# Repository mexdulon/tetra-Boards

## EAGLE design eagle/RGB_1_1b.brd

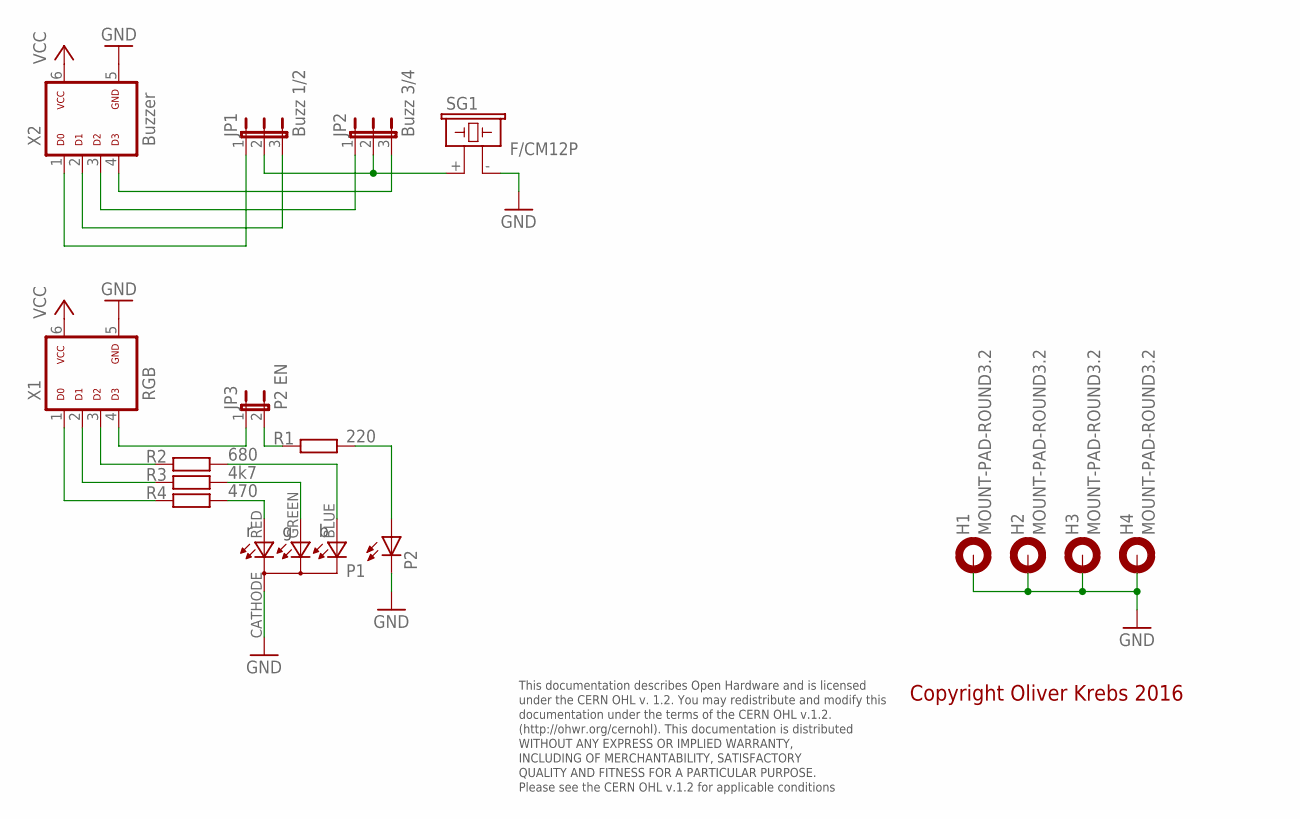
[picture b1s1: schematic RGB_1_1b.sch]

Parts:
H1, H2, H3, H4: MOUNT-PAD-ROUND3.2; 3,2-PAD
JP1: Buzz 1/2; JP2
JP2: Buzz 3/4; JP2
JP3: P2 EN; JP1
P1: RGB-5MM; RGB5MM
P2: LED5MM
R1: 220; 0207/10
R2: 680; 0207/10
R3: 4k7; 0207/10
R4: 470; 0207/10
SG1: F/CM12P
X1: RGB; ML-6
X2: Buzzer; ML-6

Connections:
GND: H1.B3,2, H2.B3,2, H3.B3,2, H4.B3,2, P1.CATHODE, P2.K (C), SG1.- (2), X1.5, X2.5
unnamed: JP1.2, JP2.2, SG1.+ (1)
unnamed: JP3.1, X1.4
unnamed: JP1.1, X2.1
unnamed: JP1.3, X2.2
unnamed: JP2.1, X2.3
unnamed: JP2.3, X2.4
unnamed: R2.1, X1.3
unnamed: R4.1, X1.1
unnamed: R3.1, X1.2
unnamed: P1.RED (A-RED), R4.2
unnamed: P1.GREEN (A-GREEN), R3.2
unnamed: P1.BLUE (A-BLUE), R2.2
unnamed: P2.A, R1.2
unnamed: JP3.2, R1.1
VCC: X1.6, X2.6

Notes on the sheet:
This documentation describes Open Hardware and is licensed under the CERN OHL v. 1.2. You may redistribute and modify this documentation under the terms of the CERN OHL v.1.2. (http://ohwr.org/cernohl). This documentation is distributed WITHOUT ANY EXPRESS OR IMPLIED WARRANTY, INCLUDING OF MERCHANT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
Copyright Oliver Krebs 2016

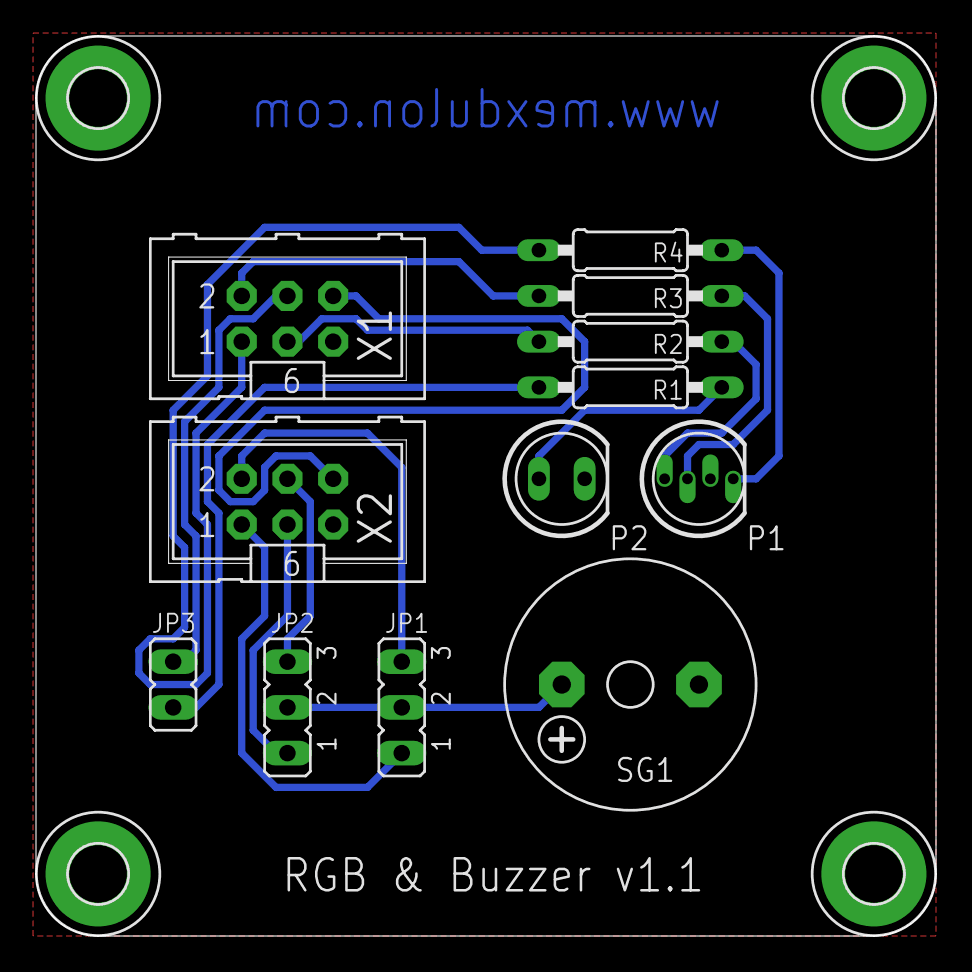
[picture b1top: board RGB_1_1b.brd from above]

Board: 2 copper layers, 50.0 x 50.0 mm, 16 parts (0 on the bottom side), 16 nets.

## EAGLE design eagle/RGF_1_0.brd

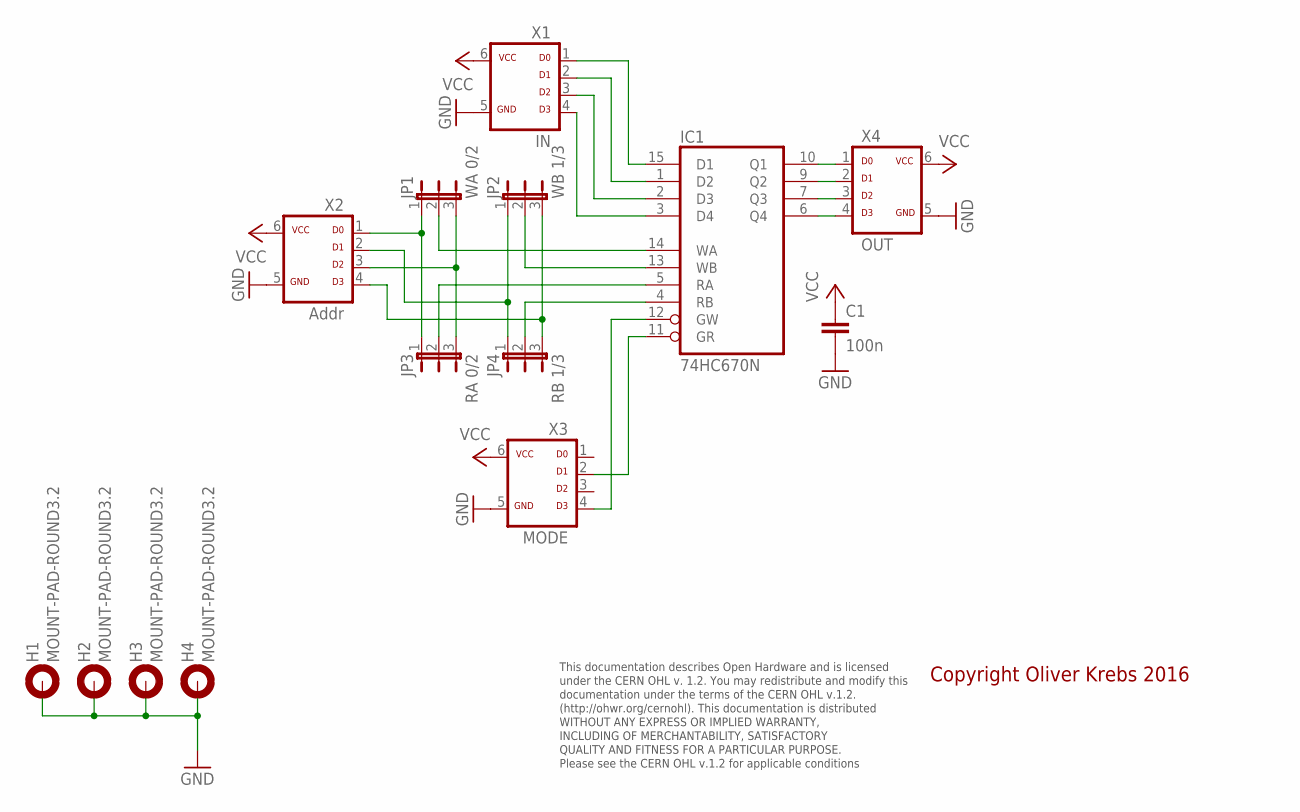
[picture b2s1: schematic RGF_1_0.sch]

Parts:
C1: 100n; C050-025X075
H1, H2, H3, H4: MOUNT-PAD-ROUND3.2; 3,2-PAD
IC1: 74HC670N; DIL16
JP1: WA 0/2; JP2
JP2: WB 1/3; JP2
JP3: RA 0/2; JP2
JP4: RB 1/3; JP2
X1: IN; ML-6
X2: Addr; ML-6
X3: MODE; ML-6
X4: OUT; ML-6

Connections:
GND: C1.2, H1.B3,2, H2.B3,2, H3.B3,2, H4.B3,2, IC1.8 (GND), X1.5, X2.5, X3.5, X4.5
unnamed: IC1.15 (D1), X1.1
unnamed: IC1.1 (D2), X1.2
unnamed: IC1.2 (D3), X1.3
unnamed: IC1.3 (D4), X1.4
unnamed: IC1.9 (Q2), X4.2
unnamed: IC1.10 (Q1), X4.1
unnamed: IC1.7 (Q3), X4.3
unnamed: IC1.6 (Q4), X4.4
unnamed: JP1.1, JP3.1, X2.1
unnamed: JP1.3, JP3.3, X2.3
unnamed: IC1.14 (WA), JP1.2
unnamed: IC1.13 (WB), JP2.2
unnamed: JP2.3, JP4.3, X2.4
unnamed: JP2.1, JP4.1, X2.2
unnamed: IC1.4 (RB), JP4.2
unnamed: IC1.5 (RA), JP3.2
unnamed: IC1.12 (GW), X3.4
unnamed: IC1.11 (GR), X3.2
VCC: C1.1, IC1.16 (VCC), X1.6, X2.6, X3.6, X4.6

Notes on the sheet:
This documentation describes Open Hardware and is licensed under the CERN OHL v. 1.2. You may redistribute and modify this documentation under the terms of the CERN OHL v.1.2. (http://ohwr.org/cernohl). This documentation is distributed WITHOUT ANY EXPRESS OR IMPLIED WARRANTY, INCLUDING OF MERCHANT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
Copyright Oliver Krebs 2016

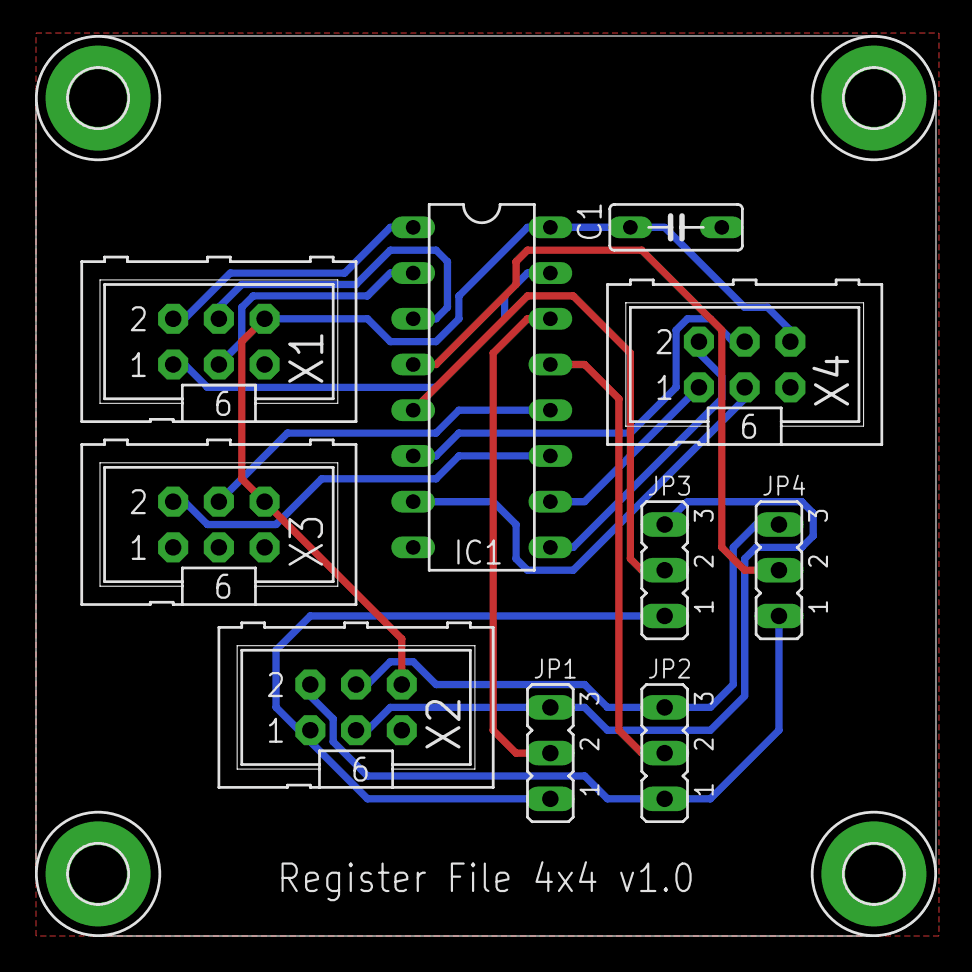
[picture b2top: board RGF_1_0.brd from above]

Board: 2 copper layers, 50.0 x 50.0 mm, 14 parts (0 on the bottom side), 20 nets.

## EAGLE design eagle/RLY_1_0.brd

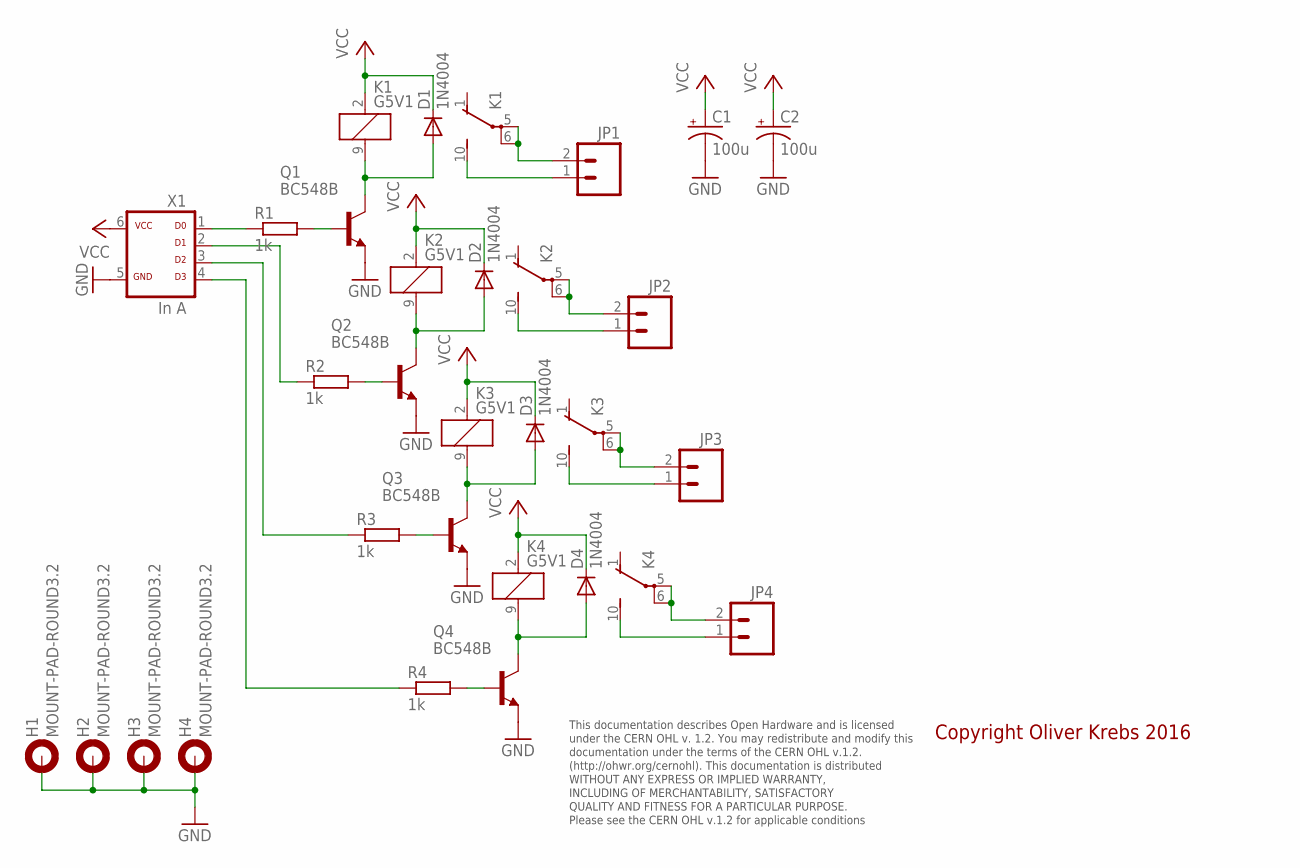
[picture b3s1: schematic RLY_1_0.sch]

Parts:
C1, C2: 100u; CPOL-RADIAL-100UF-25V
D1, D2, D3, D4: 1N4004; DO41-10
H1, H2, H3, H4: MOUNT-PAD-ROUND3.2; 3,2-PAD
JP1, JP2, JP3, JP4: M021.3MM-5.08; 1X02_BIG_5.08
K1, K2, K3, K4: G5V1
Q1, Q2, Q3, Q4: BC548B; TO92-EBC
R1, R2, R3, R4: 1k; 0207/10
X1: In A; ML-6

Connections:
GND: C1.2 (-), C2.2 (-), H1.B3,2, H2.B3,2, H3.B3,2, H4.B3,2, Q1.E, Q2.E, Q3.E, Q4.E, X1.5
unnamed: Q1.B, R1.2
unnamed: D1.A, K1.9 (2), Q1.C
unnamed: JP1.1, K1.10 (S)
unnamed: JP1.2, K1.5, K1.6
unnamed: Q2.B, R2.2
unnamed: D2.A, K2.9 (2), Q2.C
unnamed: JP2.1, K2.10 (S)
unnamed: JP2.2, K2.5, K2.6
unnamed: Q3.B, R3.2
unnamed: D3.A, K3.9 (2), Q3.C
unnamed: JP3.1, K3.10 (S)
unnamed: JP3.2, K3.5, K3.6
unnamed: Q4.B, R4.2
unnamed: D4.A, K4.9 (2), Q4.C
unnamed: JP4.1, K4.10 (S)
unnamed: JP4.2, K4.5, K4.6
unnamed: R1.1, X1.1
unnamed: R2.1, X1.2
unnamed: R3.1, X1.3
unnamed: R4.1, X1.4
VCC: C1.1 (+), C2.1 (+), D1.C, D2.C, D3.C, D4.C, K1.2 (1), K2.2 (1), K3.2 (1), K4.2 (1), X1.6

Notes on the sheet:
This documentation describes Open Hardware and is licensed under the CERN OHL v. 1.2. You may redistribute and modify this documentation under the terms of the CERN OHL v.1.2. (http://ohwr.org/cernohl). This documentation is distributed WITHOUT ANY EXPRESS OR IMPLIED WARRANTY, INCLUDING OF MERCHANT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
Copyright Oliver Krebs 2016

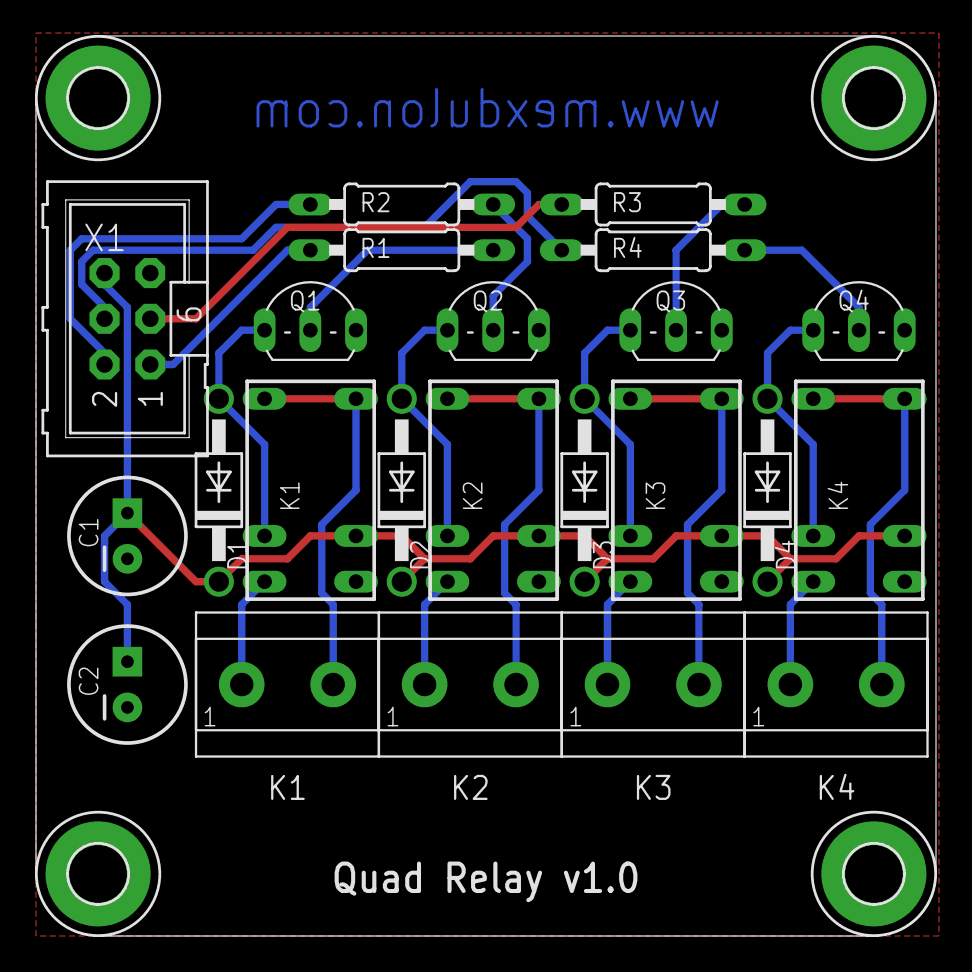
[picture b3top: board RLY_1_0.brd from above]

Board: 2 copper layers, 50.0 x 50.0 mm, 27 parts (0 on the bottom side), 22 nets.

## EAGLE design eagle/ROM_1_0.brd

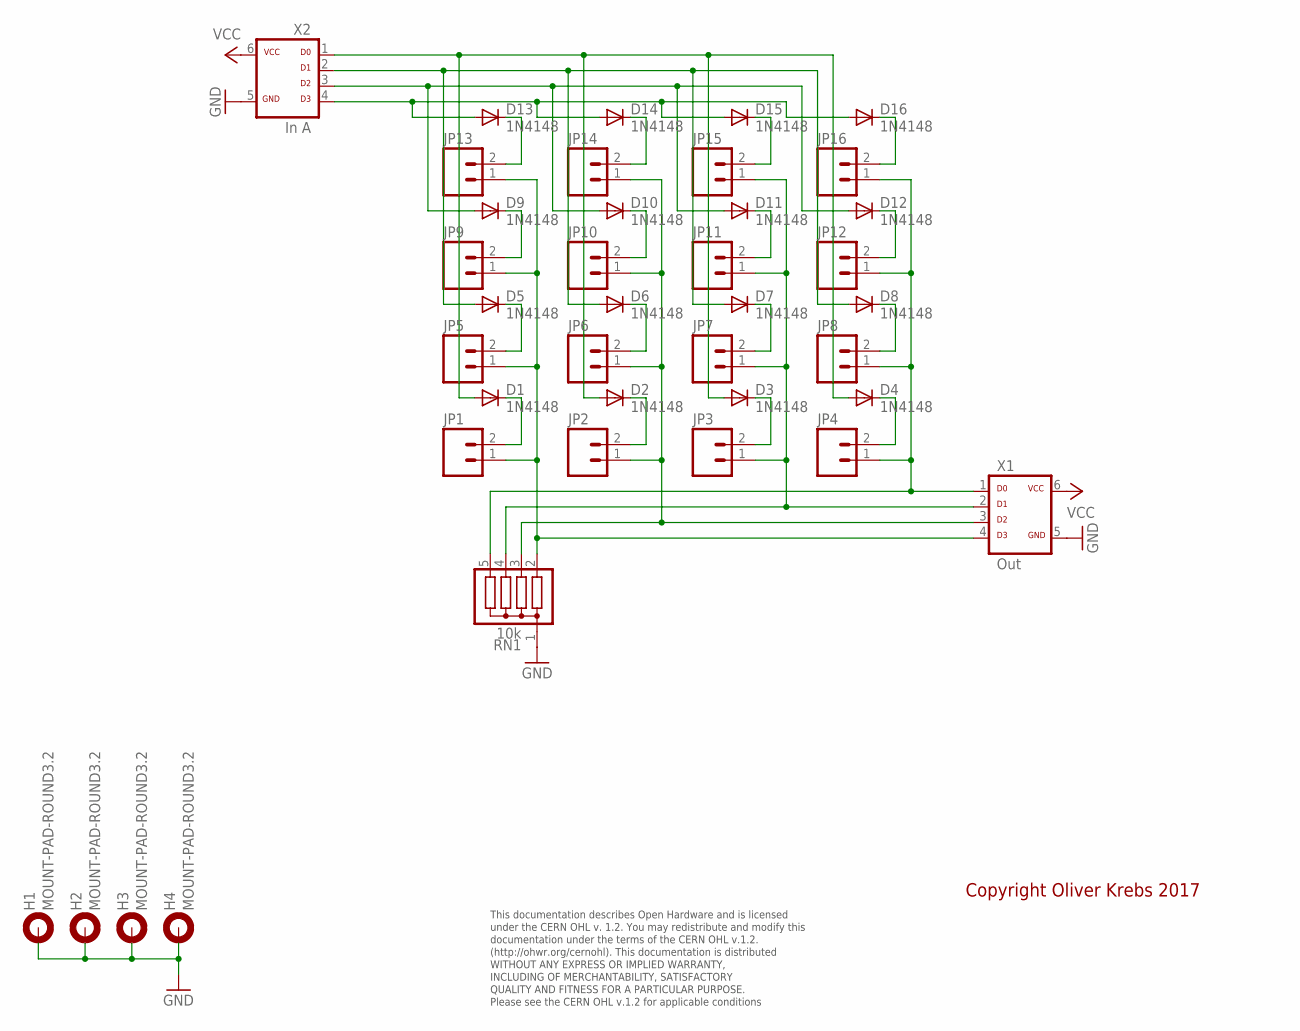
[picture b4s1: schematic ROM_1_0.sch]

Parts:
D1, D2, D3, D4, D5, D6, D7, D8, D9, D10, D11, D12, D13, D14, D15, D16: 1N4148; DO35-7
H1, H2, H3, H4: MOUNT-PAD-ROUND3.2; 3,2-PAD
JP1, JP2, JP3, JP4, JP5, JP6, JP7, JP8, JP9, JP10, JP11, JP12, JP13, JP14, JP15, JP16: M02PTH; 1X02
RN1: 10k; SIL5
X1: Out; ML-6
X2: In A; ML-6

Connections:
GND: H1.B3,2, H2.B3,2, H3.B3,2, H4.B3,2, RN1.1, X1.5, X2.5
unnamed: JP4.1, JP8.1, JP12.1, JP16.1, RN1.5, X1.1
unnamed: JP3.1, JP7.1, JP11.1, JP15.1, RN1.4, X1.2
unnamed: JP2.1, JP6.1, JP10.1, JP14.1, RN1.3, X1.3
unnamed: JP1.1, JP5.1, JP9.1, JP13.1, RN1.2, X1.4
unnamed: D1.A, D2.A, D3.A, D4.A, X2.1
unnamed: D1.C, JP1.2
unnamed: D2.C, JP2.2
unnamed: D3.C, JP3.2
unnamed: D4.C, JP4.2
unnamed: D5.A, D6.A, D7.A, D8.A, X2.2
unnamed: D6.C, JP6.2
unnamed: D7.C, JP7.2
unnamed: D5.C, JP5.2
unnamed: D8.C, JP8.2
unnamed: D9.C, JP9.2
unnamed: D10.C, JP10.2
unnamed: D11.C, JP11.2
unnamed: D12.C, JP12.2
unnamed: D9.A, D10.A, D11.A, D12.A, X2.3
unnamed: D13.A, D14.A, D15.A, D16.A, X2.4
unnamed: D13.C, JP13.2
unnamed: D14.C, JP14.2
unnamed: D15.C, JP15.2
unnamed: D16.C, JP16.2
VCC: X1.6, X2.6

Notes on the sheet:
This documentation describes Open Hardware and is licensed under the CERN OHL v. 1.2. You may redistribute and modify this documentation under the terms of the CERN OHL v.1.2. (http://ohwr.org/cernohl). This documentation is distributed WITHOUT ANY EXPRESS OR IMPLIED WARRANTY, INCLUDING OF MERCHANT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
Copyright Oliver Krebs 2017

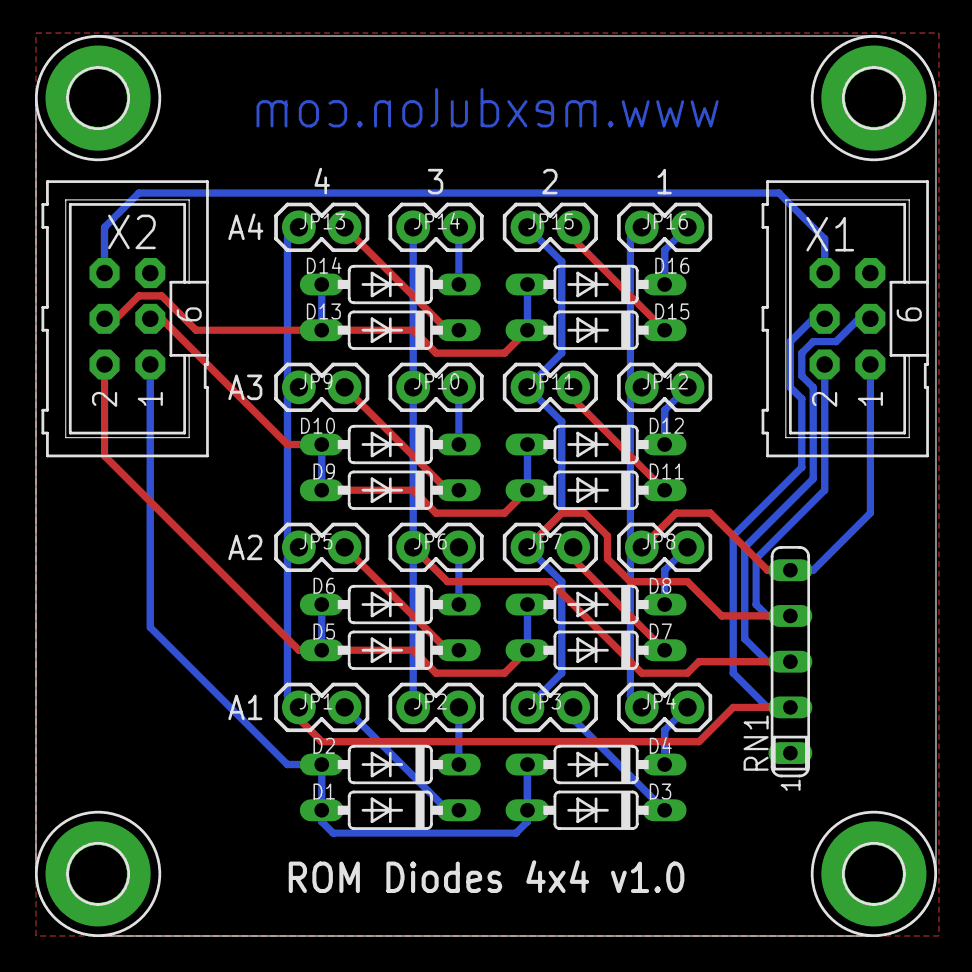
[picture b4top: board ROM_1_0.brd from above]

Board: 2 copper layers, 50.0 x 50.0 mm, 39 parts (0 on the bottom side), 26 nets.

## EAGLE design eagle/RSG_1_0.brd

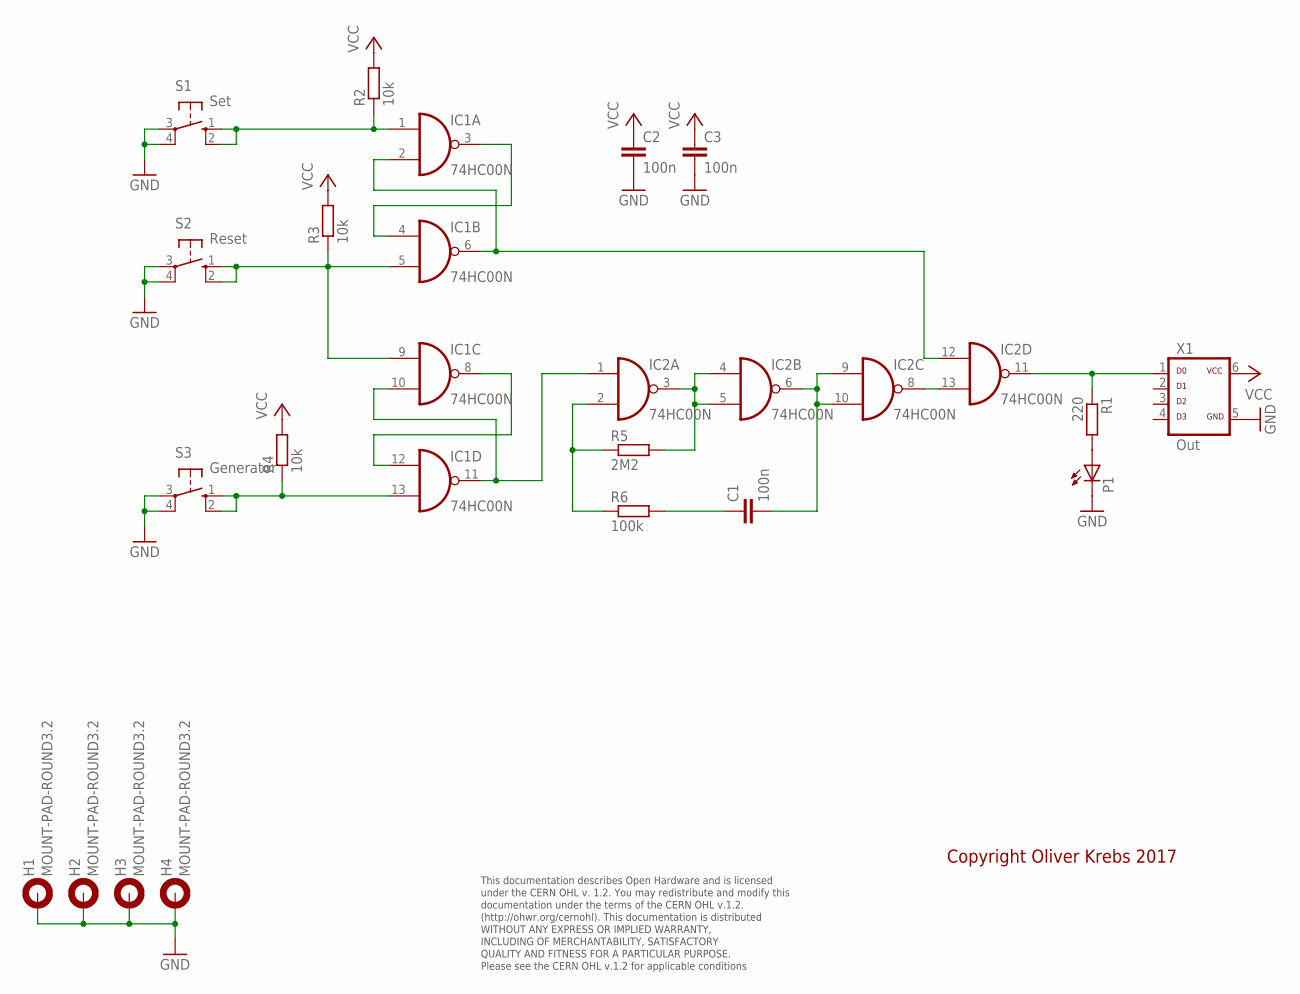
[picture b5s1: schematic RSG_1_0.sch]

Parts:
C1, C2, C3: 100n; C050-025X075
H1, H2, H3, H4: MOUNT-PAD-ROUND3.2; 3,2-PAD
IC1, IC2: 74HC00N; DIL14
P1: LED3MM
R1: 220; 0207/10
R2, R3, R4: 10k; 0207/10
R5: 2M2; 0207/10
R6: 100k; 0207/10
S1: Set; B3F-10XX
S2: Reset; B3F-10XX
S3: Generator; B3F-10XX
X1: Out; ML-6

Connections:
GND: C2.2, C3.2, H1.B3,2, H2.B3,2, H3.B3,2, H4.B3,2, IC1.7 (GND), IC2.7 (GND), P1.K (C), S1.3, S1.4 (P1), S2.3, S2.4 (P1), S3.3, S3.4 (P1), X1.5
unnamed: IC1.1 (I0), R2.1, S1.1 (S), S1.2 (S1)
unnamed: IC1.2 (I1), IC1.6 (O), IC2.12 (I0)
unnamed: IC1.3 (O), IC1.4 (I0)
unnamed: IC1.5 (I1), IC1.9 (I0), R3.1, S2.1 (S), S2.2 (S1)
unnamed: IC1.13 (I1), R4.1, S3.1 (S), S3.2 (S1)
unnamed: IC1.10 (I1), IC1.11 (O), IC2.1 (I0)
unnamed: IC1.8 (O), IC1.12 (I0)
unnamed: IC2.3 (O), IC2.4 (I0), IC2.5 (I1), R5.2
unnamed: P1.A, R1.2
unnamed: C1.2, IC2.6 (O), IC2.9 (I0), IC2.10 (I1)
unnamed: IC2.8 (O), IC2.13 (I1)
unnamed: IC2.11 (O), R1.1, X1.1
unnamed: IC2.2 (I1), R5.1, R6.1
unnamed: C1.1, R6.2
VCC: C2.1, C3.1, IC1.14 (VCC), IC2.14 (VCC), R2.2, R3.2, R4.2, X1.6

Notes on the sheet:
This documentation describes Open Hardware and is licensed under the CERN OHL v. 1.2. You may redistribute and modify this documentation under the terms of the CERN OHL v.1.2. (http://ohwr.org/cernohl). This documentation is distributed WITHOUT ANY EXPRESS OR IMPLIED WARRANTY, INCLUDING OF MERCHANT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
Copyright Oliver Krebs 2017

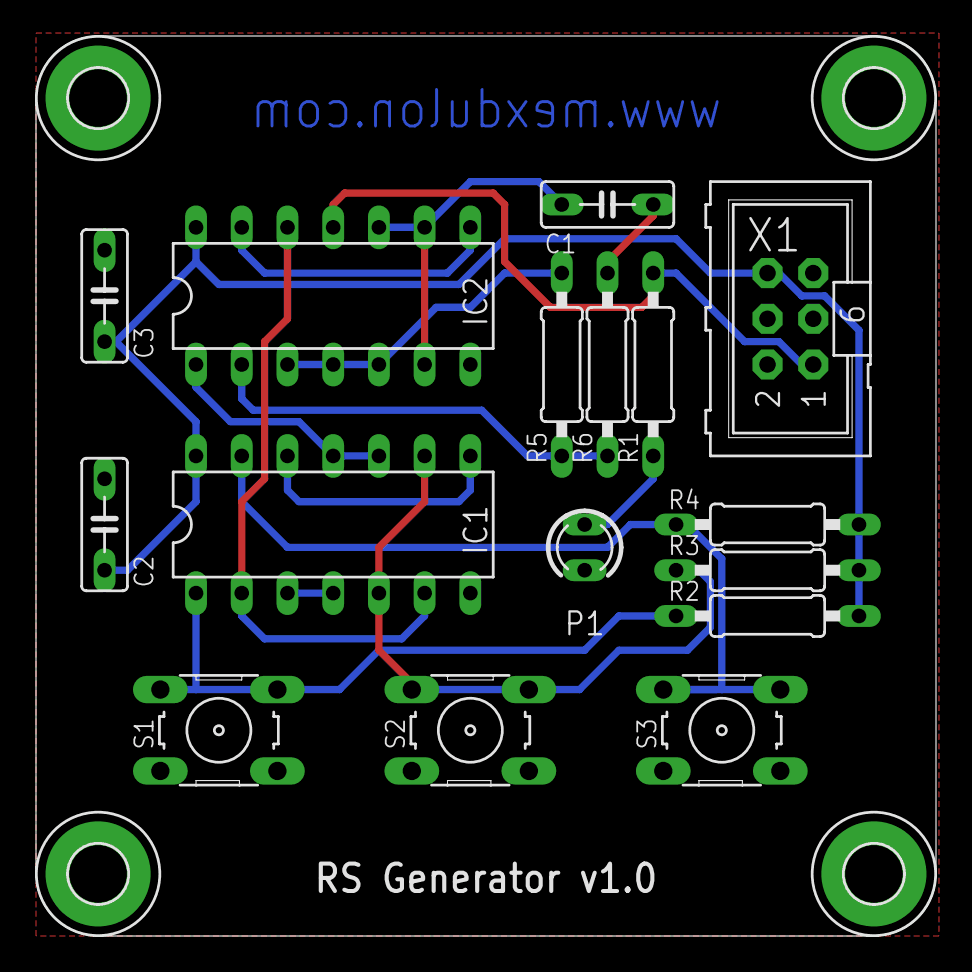
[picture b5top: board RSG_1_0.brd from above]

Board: 2 copper layers, 50.0 x 50.0 mm, 20 parts (0 on the bottom side), 16 nets.

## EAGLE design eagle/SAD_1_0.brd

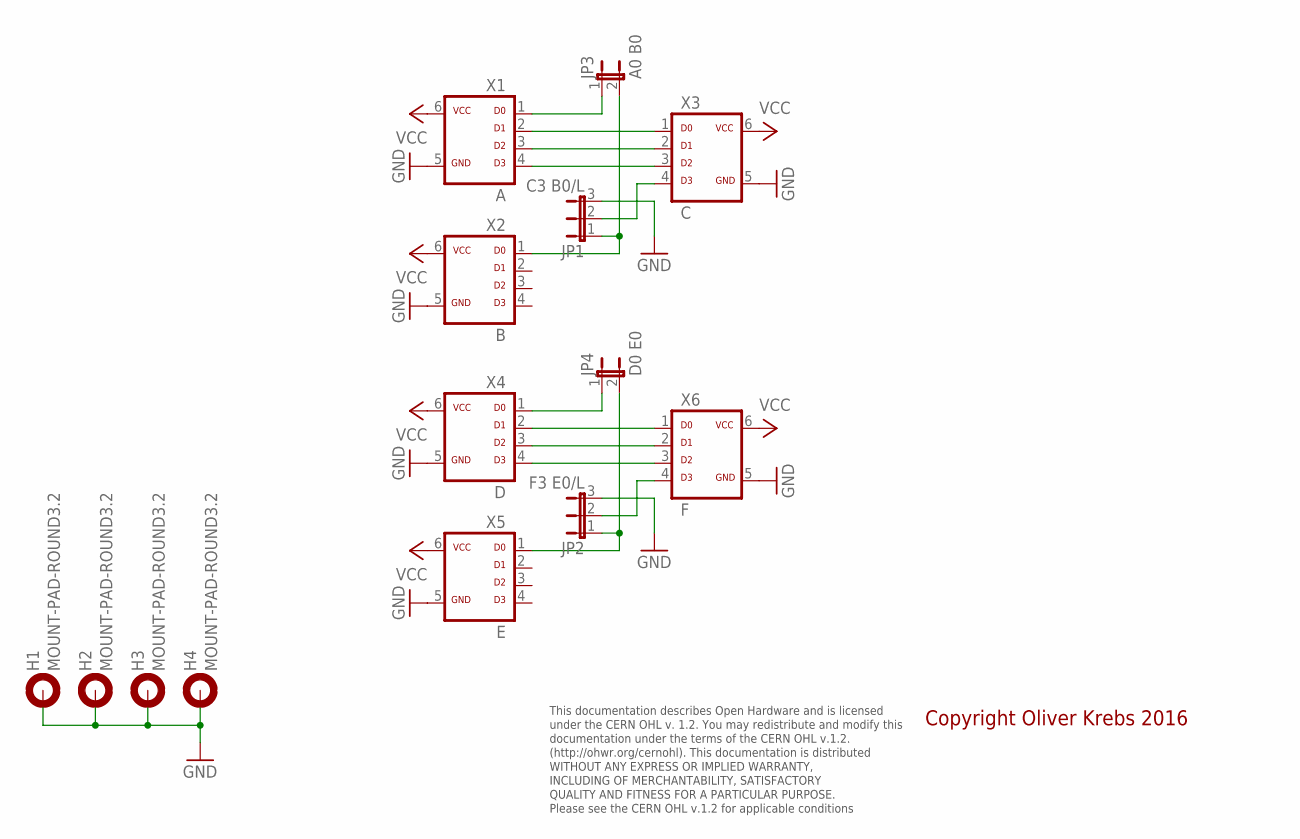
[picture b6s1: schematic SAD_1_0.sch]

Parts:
H1, H2, H3, H4: MOUNT-PAD-ROUND3.2; 3,2-PAD
JP1: C3 B0/L; JP2
JP2: F3 E0/L; JP2
JP3: A0 B0; JP1
JP4: D0 E0; JP1
X1: A; ML-6
X2: B; ML-6
X3: C; ML-6
X4: D; ML-6
X5: E; ML-6
X6: F; ML-6

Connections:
GND: H1.B3,2, H2.B3,2, H3.B3,2, H4.B3,2, JP1.3, JP2.3, X1.5, X2.5, X3.5, X4.5, X5.5, X6.5
unnamed: X1.2, X3.1
unnamed: X1.3, X3.2
unnamed: X1.4, X3.3
unnamed: JP1.2, X3.4
unnamed: JP1.1, JP3.2, X2.1
unnamed: JP4.1, X4.1
unnamed: JP3.1, X1.1
unnamed: X4.2, X6.1
unnamed: X4.3, X6.2
unnamed: X4.4, X6.3
unnamed: JP2.2, X6.4
unnamed: JP2.1, JP4.2, X5.1
VCC: X1.6, X2.6, X3.6, X4.6, X5.6, X6.6

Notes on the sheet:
This documentation describes Open Hardware and is licensed under the CERN OHL v. 1.2. You may redistribute and modify this documentation under the terms of the CERN OHL v.1.2. (http://ohwr.org/cernohl). This documentation is distributed WITHOUT ANY EXPRESS OR IMPLIED WARRANTY, INCLUDING OF MERCHANT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
Copyright Oliver Krebs 2016

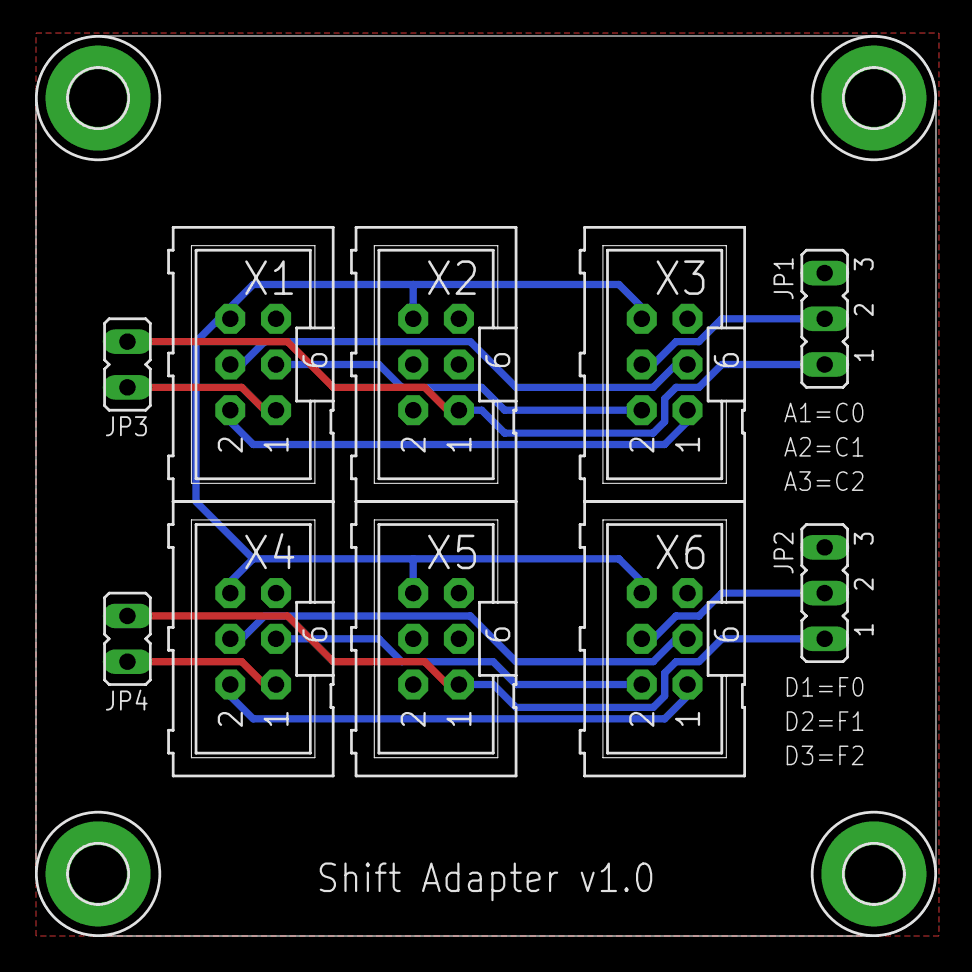
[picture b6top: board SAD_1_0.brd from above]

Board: 2 copper layers, 50.0 x 50.0 mm, 14 parts (0 on the bottom side), 14 nets.

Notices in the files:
eagle/RGB_1_1b.brd:
Licensed under CERN OHL v.1.2
parts and their libraries:
SparkFun-Connectors: Licensing: Creative Commons ShareAlike 4.0 International - https://creativecommons.org/licenses/by-sa/4.0
